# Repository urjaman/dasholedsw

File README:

I suppose i need a mission statement for this thing :P

It's a lil car widget, where the firmware is derived from a previous car widget (carlcdp).
Previously the mission was to:
- display two voltages
- control a relay based on a voltage

Other things were bonus features, like the temperature display, clock and whatnot things

This device has a mission to take in data:
- RPM pulse
- speedometer pulse
- fuel sensor voltage
(other things too, but those are bonus)

and process it into features:
- odometer 
 - trip meter
- speedometer
- RPM display

- fuel level display 
 - longer-scale derived displays like l/100km

(again, other things too, but these are the primary ones)

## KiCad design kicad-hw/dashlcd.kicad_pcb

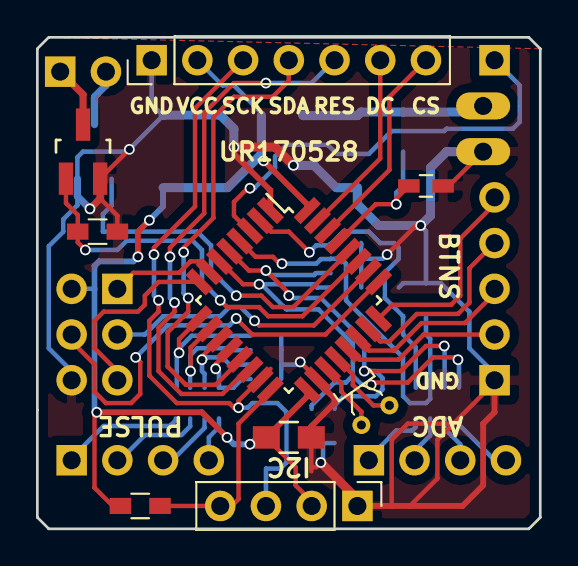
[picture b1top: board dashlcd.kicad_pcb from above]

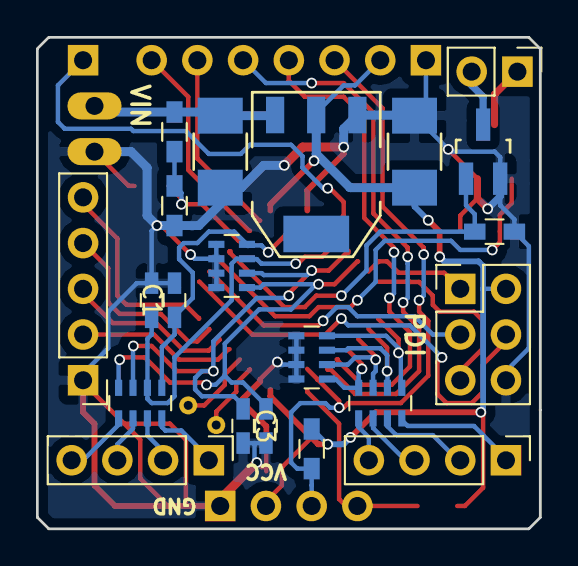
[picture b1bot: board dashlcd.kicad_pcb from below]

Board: 2 copper layers, 27.9 x 27.3 mm, 32 parts (23 on the bottom side), 41 nets.

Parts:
C1, C2, C3, C4, C5: .1u; C_0603_HandSoldering
C102, C103: 10u; C_1210_HandSoldering
C104: 1u; C_0805_HandSoldering
CON101: AVR-PDI-6; Pin_Header_Straight_2x03_Pitch2.54mm
IC101: ATXMEGA32E5-A; TQFP-32_7x7mm_Pitch0.8mm
J1: DRV; Pin_Header_Straight_1x02_Pitch2.54mm
J2: OLED_I2C; Pin_Header_Straight_1x04_Pitch2.54mm
J3: OLED_SPI; Pin_Header_Straight_1x07_Pitch2.54mm
J4: ADC; Pin_Header_Straight_1x04_Pitch2.54mm
J5: PULSE; Pin_Header_Straight_1x04_Pitch2.54mm
J6: DAC; Pin_Header_Straight_1x01_Pitch2.54mm
P1: PWR; PINHEAD1-2
P104: CONN_01X05; Pin_Header_Straight_1x05_Pitch2.54mm
Q101, Q102: IRLML6344TRPBF; SOT-23_Handsoldering
R1, R2: 2k2; R_0603_HandSoldering
R102, R107: 4k7; R_0603_HandSoldering
R108: 330k; R_0603_HandSoldering
R109: 22k; R_0603_HandSoldering
RN1, RN3: 22k; R_Array_Concave_4x0603
RN2: 330k; R_Array_Concave_4x0603
RN4: 8k2; R_Array_Concave_4x0603
U101: NCP1117ST33T3G; SOT-223
Y1: 32k; Crystal_DS26_d2.0mm_l6.0mm_Horizontal

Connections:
+3V3: C103.1, C104.1, CON101.2, IC101.17, IC101.32, J2.2, J3.2, R1.1, R2.1, U101.2
/ADCH2: C5.1, IC101.29, R108.1, R109.2
/AUX_DRV: IC101.27, Q102.1, R107.1
/BACKLIGHT: J4.4, RN2.5
/BACKLIGHTL: C4.1, IC101.6, RN1.1, RN2.4
/CS: IC101.30, J3.7
/DAC: IC101.3, J6.1
/DAUX: J5.4, RN3.1
/DAUXD: IC101.12, RN3.8, RN4.1
/DC: IC101.31, J3.6
/ECULAMP: J5.3, RN3.2
/ECULAMPD: IC101.11, RN3.7, RN4.2
/FUEL: J4.2, RN2.7
/FUELL: C2.1, IC101.4, RN1.3, RN2.2
/MOSI: IC101.13, J3.4
/R10V: J4.1, RN2.8
/R10VL: C1.1, IC101.2, RN1.4, RN2.1
/RES: IC101.14, J3.5
/RLY_DRV: IC101.28, Q101.1, R102.1
/ROADSPD: J5.2, RN3.3
/ROADSPDD: IC101.10, RN3.6, RN4.3
/RPM: J5.1, RN3.4
/RPMD: IC101.9, RN3.5, RN4.4
/SCL: IC101.15, J2.3, J3.3, R2.2
/SDA: IC101.16, J2.4, R1.2
/TEMP: J4.3, RN2.6
/TEMPL: C3.1, IC101.5, RN1.2, RN2.3
/VIN: C102.1, P1.2, R108.2, U101.3
GND: C1.2, C2.2, C3.2, C4.2, C5.2, C102.2, C103.2, C104.2, CON101.6, IC101.1, IC101.18, J2.1, J3.1, P1.1, P104.1, Q101.2, Q102.2, R102.2, R107.2, R109.1, RN1.5, RN1.6, RN1.7, RN1.8, RN4.5, RN4.6, RN4.7, RN4.8, U101.1
unnamed: CON101.1, IC101.7
unnamed: CON101.3, IC101.26
unnamed: CON101.4, IC101.25
unnamed: CON101.5, IC101.8
unnamed: IC101.19, Y1.2
unnamed: IC101.20, Y1.1
unnamed: IC101.21, P104.2
unnamed: IC101.22, P104.3
unnamed: IC101.23, P104.4
unnamed: IC101.24, P104.5
unnamed: J1.1, Q102.3
unnamed: J1.2, Q101.3

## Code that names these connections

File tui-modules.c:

#include "main.h"
#include "tui.h"
#include "tui-lib.h"
#include "tui-mod.h"
#include "adc.h"
#include "relay.h"
#include "timer.h"
#include "pulse.h"
#include "lib.h"
#include "lcd.h"
#include "speedo.h"
#include "odo.h"

int null_ps(uint8_t prv);
int null_ps(uint8_t prv)
{
	(void)prv;
	return 0;
}

static void tui_modfinish(uint8_t*t, uint8_t ml, uint8_t x, uint8_t w)
{
	t[ml] = 0;
	uint8_t mw = lcd_strwidth(t);
	if (mw > w) mw = w; // this is a problem, but i'll leave that for the mods to avoid,
	//  this just fixes math locally here :P
	uint8_t cl = w - mw;
	if ((x+w) >= LCDWIDTH) { // right align
		lcd_clear_dw(cl);
		lcd_puts_dw(t);
	} else {
		lcd_puts_dw(t);
		lcd_clear_dw(cl);
	}
}

static uint8_t tui_ch_char(uint8_t ch)
{
	if (ch==ADC_CH_BACKLIGHT) return 'L';
	if (ch==ADC_CH_TEMP) return 'T';
	if (ch==ADC_CH_FUEL) return 'F';
	if (ch==ADC_CH_R10V) return 'R';
	if (ch==ADC_CH_MB) return 'M';
	return '?';
}

static const unsigned char tui_adcch_s0[] PROGMEM = "BACKLIGHT";
static const unsigned char tui_adcch_s1[] PROGMEM = "TEMP";
static const unsigned char tui_adcch_s2[] PROGMEM = "FUEL";
static const unsigned char tui_adcch_s3[] PROGMEM = "10V REF";
static const unsigned char tui_adcch_s4[] PROGMEM = "INPUT VOLTS";
static PGM_P const tui_adcch_table[] PROGMEM = {
	(PGM_P)tui_adcch_s0,
	(PGM_P)tui_adcch_s1,
	(PGM_P)tui_adcch_s2,
	(PGM_P)tui_adcch_s3,
	(PGM_P)tui_adcch_s4,
	(PGM_P)tui_exit_menu,
};

int tui_adcsel(uint8_t par);
int tui_adcsel(uint8_t par)
{
	par = tui_gen_listmenu(PSTR("ADC CHANNEL"), tui_adcch_table, 6, par);
	if (par >= 5) return -1;
	return par;
}

static void tui_gbv_mod(uint8_t x, uint8_t c1, uint8_t c2, uint16_t v)
{
	uint8_t mb[9];
	mb[0] = c1;
	mb[1] = c2;
	adc_print_v(&(mb[2]),v);
	tui_modfinish(mb,8,x,8*LCD_CHARW);
}

TUI_MOD(tui_bv_mod,tui_adcsel,"Volts (AVG)",8*LCD_CHARW,1)
{
	tui_gbv_mod(x, tui_ch_char(par), ':', adc_read_ch(par));
}

TUI_MOD(tui_maxbv_mod,tui_adcsel,"Volts (MAX)",8*LCD_CHARW,1)
{
	tui_gbv_mod(x, tui_ch_char(par), '+', adc_read_maxv(par));
}

TUI_MOD(tui_minbv_mod,tui_adcsel,"Volts (MIN)",8*LCD_CHARW,1)
{
	tui_gbv_mod(x, tui_ch_char(par), '-', adc_read_minv(par));
}

TUI_MOD(tui_ripple_mod,tui_adcsel,"Ripple",8*LCD_CHARW,1)
{
	tui_gbv_mod(x, tui_ch_char(par), 'R', adc_read_maxv(par)-adc_read_minv(par));
}


TUI_MOD(tui_rlst_mod,null_ps,"Relay Info",5*LCD_CHARW,1)
{
	uint8_t mb[6];
	mb[0] = 'R';
	mb[1] = ':';
	switch (relay_get_mode()) {
		default:
		case RLY_MODE_OFF:
			mb[2] = '0';
			break;
		case RLY_MODE_ON:
			mb[2] = '1';
			break;
		case RLY_MODE_AUTO:
			mb[2] = 'A';
			break;
	}
	mb[3] = '>'; // "->"-like char
	switch (relay_get()) {
		default:
		case RLY_MODE_OFF:
			mb[4] = '0';
			break;
		case RLY_MODE_ON:
			mb[4] = '1';
			break;
	}
	tui_modfinish(mb,5,x,5*LCD_CHARW);
}


static const unsigned char tui_pch_s0[] PROGMEM = "DAUX";
static const unsigned char tui_pch_s1[] PROGMEM = "ECULAMP";
static const unsigned char tui_pch_s2[] PROGMEM = "ROADSPD";
static const unsigned char tui_pch_s3[] PROGMEM = "RPM";
static PGM_P const tui_pch_table[] PROGMEM = {
	(PGM_P)tui_pch_s0,
	(PGM_P)tui_pch_s1,
	(PGM_P)tui_pch_s2,
	(PGM_P)tui_pch_s3,
	(PGM_P)tui_exit_menu,
};

int tui_pulsesel(uint8_t par);
int tui_pulsesel(uint8_t par)
{
	par = tui_gen_listmenu(PSTR("Channel"), tui_pch_table, 5, par);
	if (par >= 4) return -1;
	return par;
}


TUI_MOD(tui_pstate_mod,tui_pulsesel,"Edge Ctr",8*LCD_CHARW,1)
{
	uint8_t buf[9];
	uint16_t e;
	uint8_t s = pulse_state(par+4, &e);
	buf[0] = '4'+par;
	buf[1] = ':';
	buf[2] = '0'+s;
	buf[3] = '|';
	uchar2xstr(buf+4, e>>8);
	uchar2xstr(buf+6, e&0xFF);
	tui_modfinish(buf,8,x,8*LCD_CHARW);
}

TUI_MOD(tui_pulsehz_mod,tui_pulsesel,"Freq",9*LCD_CHARW,1)
{
	uint8_t buf[10];
	uint24_t hz = pulse_get_hz(par+4, NULL);
	buf[0] = '4'+par;
	buf[1] = ':';
	uint24_t hzi = hz >> PULSE_HZ_SHIFT;
	if (hzi>99999) hzi = 99999;
	uint8_t n = luint2str(buf+2, hzi) + 2;
	buf[n] = '.';
	buf[n+1] = '0' + ( (hz & (_BV(PULSE_HZ_SHIFT)-1) * 10) >> PULSE_HZ_SHIFT );
	buf[n+2] = 0;
 	tui_modfinish(buf,n+2,x,9*LCD_CHARW);
}


TUI_MOD(tui_speedo_mod,null_ps,"Speedo", 6*LCD_CHARW,2)
{
	const uint8_t lcdw = 6*LCD_CHARW;
	uint8_t buf[8];
	uint16_t kmh = (speedo_get_kmh10()+5)/10;
	if (kmh>999) kmh=999;
	uint2str(buf,kmh);
	uint8_t off = lcdw - lcd_strwidth_big(buf);
	lcd_clear_big_dw(off);
	lcd_puts_big(buf);
}

TUI_MOD(tui_big_speedo_mod,null_ps,"Big Speedo", 12*LCD_CHARW, 4)
{
	const uint8_t lcdw = 12*LCD_CHARW;
	uint8_t buf[8];
	uint16_t kmh = (speedo_get_kmh10()+5)/10;
	if (kmh>999) kmh=999;
	uint2str(buf,kmh);
	uint8_t off = lcdw - lcd_strwidth_dbig(buf);
	lcd_clear_dbig_dw(off);
	lcd_puts_dbig(buf);
}

TUI_MOD(tui_odometer_mod,null_ps,"Odometer", 12*LCD_CHARW, 4)
{
	uint8_t buf[8];
	uint32_t m = odo_get(NULL);
	uint24_t km = m/1000;
	m = m%1000;
	if (km>999999) km %= 1000000;
	luint2str_zp(buf, km, 6);
	tui_set_color(TTC_HL1);
	lcd_puts_big(buf);
	tui_unset_color();

	lcd_gotoxy_dw(x,y+2);
	luint2str_zp(buf, m, 3);
	lcd_puts(buf);

	PGM_P kms = PSTR("KM");
	uint8_t skip = 1*LCD_CHARW;
	lcd_clear_big_dw(skip);
	tui_set_color(TTC_HEAD1);
	lcd_puts_big_P(kms);
	tui_unset_color();
	lcd_clear_big_eol();

	lcd_gotoxy_dw(x,y+3);
	lcd_clear_dw(4*LCD_CHARW);
}

TUI_MOD(tui_rpm_mod,null_ps,"RPM", LCDWIDTH, 1)
{
	const int rpm_mul = 30;
	const int rpm_per_px = 75;
	const int redline = 6400;
	const int optimum = 2600;

	uint8_t dbuf[LCDWIDTH];
	uint16_t rpm = (pulse_get_hz(PCH_RPM, NULL) * rpm_mul) >> PULSE_HZ_SHIFT;


	//unsigned char rpms[5];
	//luint2str_zp(rpms, rpm%10000, 4);
	//uint8_t strw = lcd_get_strbuf(dbuf, rpms, 0);
	memset(dbuf, 0, LCDWIDTH);

	/* Tack the 1000 RPM indicators in there */
	const int maxrpm = LCDWIDTH*rpm_per_px;
	for (int i=1000; i < maxrpm;i += 1000) {
		dbuf[(i + (rpm_per_px/2)) / rpm_per_px] |= 0x7;
	}

	/* Put the Redline in there */
	uint8_t rlpix = (redline + (rpm_per_px/2)) / rpm_per_px;
	dbuf[rlpix] |= 0x3F;

	uint8_t rpmpix = (rpm + (rpm_per_px/2)) / rpm_per_px;

	uint16_t rpmbg;
	if (rpm>=redline) {
		rpmbg = rgb(255,0,0);
	} else if (rpm<=optimum) {
		uint16_t hp = optimum/2;
		uint8_t g,b;
		if (rpm<=hp) {
			g = (rpm * 255UL) / hp;
			b = 255;
		} else {
			g = 255;
			b = 255 - ( ((rpm - hp) * 255UL) / (optimum - hp) );
		}
		rpmbg = rgb(0,g,b);
	} else {
		uint16_t zt = redline - optimum;
		uint16_t zn = rpm - optimum;
		uint16_t zh = zt / 2;
		uint8_t r,g;
		if (zn<=zh) {
			r = (zn * 255UL) / zh;
			g = 255;
		} else {
			r = 255;
			g = 255 - ( ((zn - zh) * 255UL) / (zt - zh) );
		}
		rpmbg = rgb(r,g,0);
	}
	const uint8_t r1 = rpmpix > rlpix ? rlpix : rpmpix;
	const uint8_t n1 = rlpix - r1;
	const uint8_t r2 = rpmpix > rlpix ? rpmpix - rlpix : 0;
	const uint8_t n2 = (LCDWIDTH - rlpix) - r2;

	const uint16_t white = rgb(255, 255, 255);
	const uint16_t black = rgb(0, 0, 0);
	if (r1) {
		dp_set_fg_bg(white, rpmbg);
		lcd_write_dwb(dbuf, r1);
	}
	if (n1) {
		dp_set_fg_bg(white, black);
		lcd_write_dwb(dbuf+r1, n1);
	}
	uint16_t rlc = rgb(128,8,0);
	if (r2) {
		dp_set_fg_bg(rlc, rpmbg);
		lcd_write_dwb(dbuf+r1+n1, r2);
	}
	if (n2) {
		dp_set_fg_bg(rlc, black);
		lcd_write_dwb(dbuf+r1+n1+r2, n2);
	}
	tui_default_color();
}

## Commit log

2016-03-29 switch to the mini-lcd voltage indicator thingy
2016-03-30 middle of something
2016-04-06 pcd8544: move to hw spi
2016-04-06 pcd8544: spi... better or fail, but different
2016-04-07 adc: maybe ...
2016-04-07 improved lcd stuff, clear()ier tui...
    now... why 5.16V?
2016-04-07 adc: operational :)
2016-04-07 tui: show dem adc ch's
2016-04-07 adc: flush bad sample(s) on boot
    this makes for much cleaner first reading on boot :)
2016-04-08 pcd8544: switch to async SPI code...
2016-04-08 buttons: support 1, 2, 3 or 4 buttons :P
    with 1 button you'll need to live with next or ok, but yeah
    they should be enough to navigate our menus, though slowly...
2016-04-08 improve buttons ...
2016-04-09 lcd improvements in preparation for fancier "T"UI :P
2016-04-09 tui-lib: stuff for an UI...
2016-04-10 tui: fixup some, add some menus etc
2016-04-10 Make the UI fit better on the 84x48 LCD ...
2016-04-10 lcd: add sane edge clipping ...
2016-04-10 make the TUI a bit easier to use with 1 button
2017-06-20 this was how the PCD8544 version was left, now to modify
2017-06-21 Dash-OLED has born :)
2017-06-22 get rid of 5110 lcd text alignment
2017-06-22 nasty menu bug fixed and menu stuff reworked lots
2017-06-22 support oled "backlight" (brightness) control
2017-06-22 adc: support the 5 channels we have
2017-06-22 fixup/remove flicery-looking unnecessary lcd-clears
2017-06-22 Hook up TUI modules from iblcdp
2017-06-22 Implement one button mode for the TUI module editor
2017-06-22 update ignore for the generated TUI db
2017-06-23 pass astyle on the whole project :)
2017-06-24 Add the saver module (not yet functional, suspecting the avr-libc EEPROM driver, writing own...)
2017-06-24 EEPROM worky :)
2017-06-24 add saver API support to backlight and relay modules
2017-06-25 add support for forcing backlight on at the "drive" level
2017-06-25 move system timer to TCD5, freeing TCC4 for capture operations
    plans: TCD5 for system timer
    TCC4 for 4-channel frequency capture (one or both edges, i guess...)
    TCC5 for 1-channel frequency and duty capture
2017-06-27 welcome the pulse module :)
2017-06-27 some mostly-debug TUI modules to use the pulse API
2017-06-28 fixup logic so pulse actually clears to 0 Hz properly :)
2017-06-28 add option to obtain the age of pulse frequency data :)
2017-06-28 add support for multiple TUI main-screen pages
2017-06-29 moved timer subsystem to live from the 32kHz RTC module
2017-06-29 pulse: use 8192 Hz from the 32.768kHz crystal for timing
    should be able to have accurate RPM and speed ;P
2017-06-29 fixup comp match updating, add (disabled) CPU frequency measurement code
2017-06-30 tui-mod: encode module count in stored EEPROM size
    this way we can freely change TUI_MODS_MAX without breaking compatibility,
    and save a byte (plus 4* unused module slots) of EEPROM :)
2017-07-01 initial version of the new speedo module (untested)
2017-07-01 implement a couple of speedometers
2017-07-01 make numbers fixed-width
2017-07-01 Move xmega32e5 EEPROM code from saver.c to ee.{c,h}
2017-07-03 EEPROM-based counter (for odometer, or similar) initial implementation (untested)
2017-07-05 add odometer module (no users yet)
2017-07-06 simplify a little
2018-05-10 apply the name ... and this is how i left it
2018-05-10 fix odometer
2018-05-10 add some sort of a doc
2018-05-11 better module names
2018-05-11 basic color theme support, with a horrible and more horrible theme lol
2018-05-27 Boot logo support :)
    My current logo i'm using is copyrighted so you dont get logo.gif,
    but maybe i'll put some test data in later, also you can just
    make your own 96x64 low-color gif you like :)
2018-05-27 Add the kicad hardware files
2018-05-28 USART MSPIM for LCD SPI support (untested, yet)
2018-05-28 fixup that MSPIM support, and change it to ISR-less
    the display is initialized and used so early that we dont have
    interrupts running, maybe to be fixed but work with that.
2018-05-28 cleanup the OLED driver (get rid of the bitbang option etc)
2018-05-29 optimize SSD1331 initialization
    smaller code ftw
2018-05-29 set precharge C as the code was apparently supposed to do
    I see no big difference in how the image looks tbh, and
    i'm not sure what the precharge value for C would
    actually be optimal... *sigh*
2018-05-29 Make the picked theme save, and make the red theme sane
2018-05-30 fix up and down edges of blobs in TUI editor
    swappyti swap
2018-05-30 pretty RPM gauge, to be redesigned, but for storage :P
2018-06-02 a bit simpler, a bit clearer RPM gauge
2018-06-02 varying pulse simulator...
